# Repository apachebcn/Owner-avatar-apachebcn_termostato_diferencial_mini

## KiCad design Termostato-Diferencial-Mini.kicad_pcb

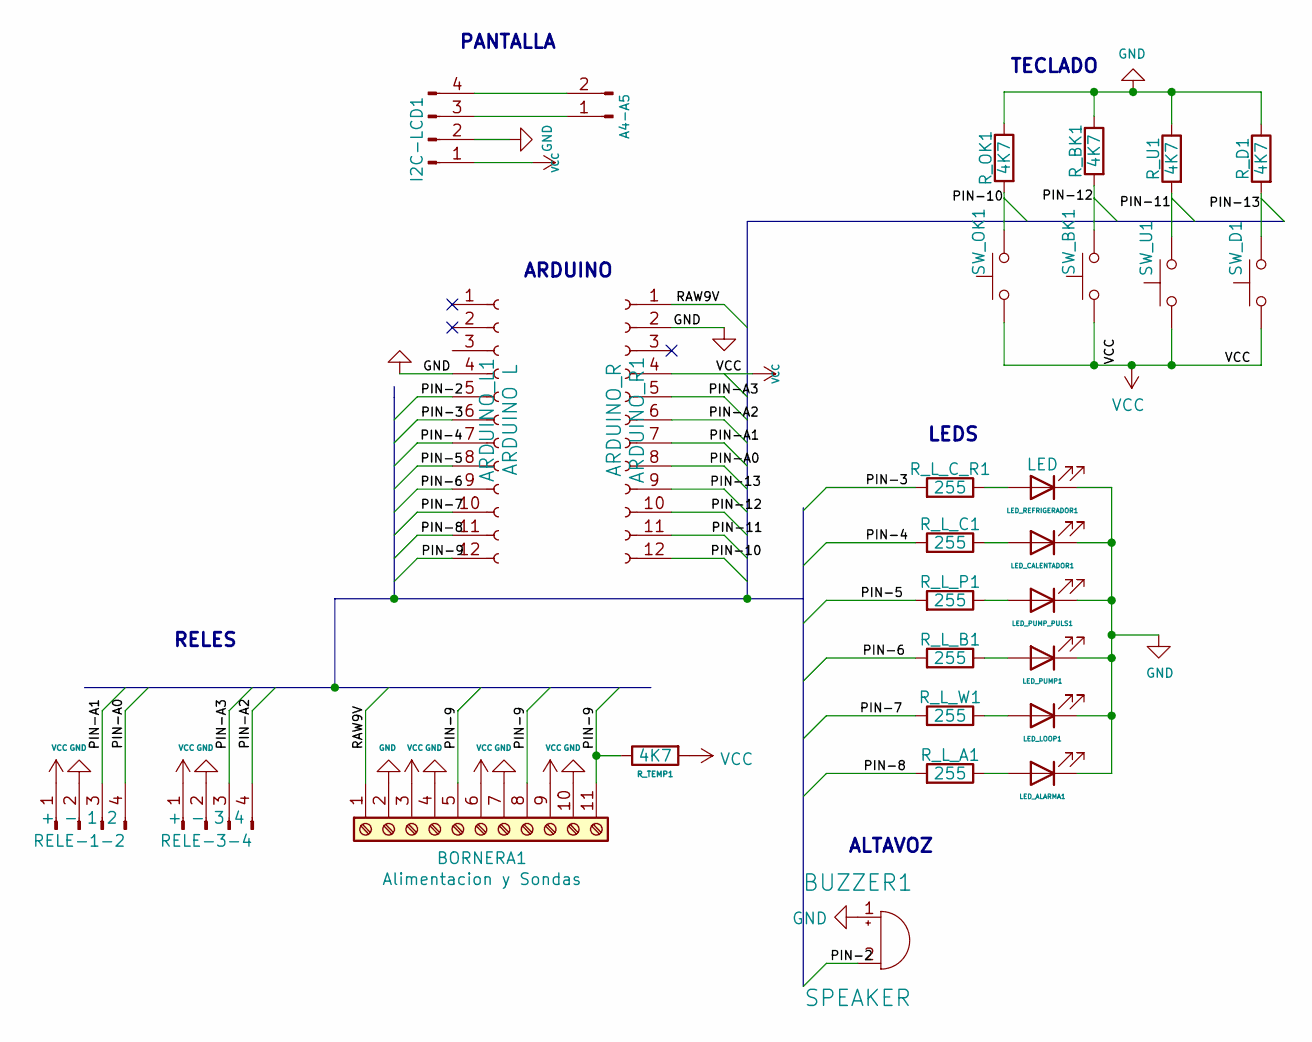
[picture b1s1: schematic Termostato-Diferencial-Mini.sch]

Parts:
A4-A5: CONN_2; PinHeader_1x02_P2.54mm_Vertical
ARDUINO_L1: ARDUINO L; PinSocket_1x13_P2.54mm_Vertical
ARDUINO_R1: ARDUINO_R; PinSocket_1x13_P2.54mm_Vertical
BORNERA1: Alimentacion y Sondas; TerminalBlock_Phoenix_MKDS-3-11-5.08_1x11_P5.08mm_Horizontal
BUZZER1: SPEAKER; Buzzer_12x9.5RM7.6
I2C-LCD1: CONN_4; PinHeader_1x04_P2.54mm_Horizontal
LED_ALARMA1: LED; LED_1206_3216Metric
LED_CALENTADOR1: LED; LED_1206_3216Metric
LED_LOOP1: LED; LED_1206_3216Metric
LED_PUMP1: LED; LED_1206_3216Metric
LED_PUMP_PULS1: LED; LED_1206_3216Metric
LED_REFRIGERADOR1: LED; LED_1206_3216Metric
RELE-1-2: + - 1 2; PinHeader_1x04_P2.54mm_Horizontal
RELE-3-4: + - 3 4; PinHeader_1x04_P2.54mm_Horizontal
R_BK1: 4K7; R_1206_3216Metric
R_D1: 4K7; R_1206_3216Metric
R_L_A1: 255; R_1206_3216Metric
R_L_B1: 255; R_1206_3216Metric
R_L_C1: 255; R_1206_3216Metric
R_L_C_R1: 255; R_1206_3216Metric
R_L_P1: 255; R_1206_3216Metric
R_L_W1: 255; R_1206_3216Metric
R_OK1: 4K7; R_1206_3216Metric
R_TEMP1: 4K7; R_1206_3216Metric
R_U1: 4K7; R_1206_3216Metric
SW_BK1: SW; SW_PUSH-12mm
SW_D1: SW; SW_PUSH-12mm
SW_OK1: SW; SW_PUSH-12mm
SW_U1: SW; SW_PUSH-12mm

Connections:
/PIN-2: ARDUINO_L1.5, BUZZER1.2 (+)
/PIN-3: ARDUINO_L1.6, R_L_C_R1.2
/PIN-4: ARDUINO_L1.7, R_L_C1.2
/PIN-5: ARDUINO_L1.8, R_L_P1.2
/PIN-6: ARDUINO_L1.9, R_L_B1.2
/PIN-7: ARDUINO_L1.10, R_L_W1.2
/PIN-8: ARDUINO_L1.11, R_L_A1.2
/PIN-9: ARDUINO_L1.12, BORNERA1.5, BORNERA1.8, BORNERA1.11, R_TEMP1.1
/PIN-10: ARDUINO_R1.12, R_OK1.2, SW_OK1.2
/PIN-11: ARDUINO_R1.11, R_U1.2, SW_U1.2
/PIN-12: ARDUINO_R1.10, R_BK1.2, SW_BK1.2
/PIN-13: ARDUINO_R1.9, R_D1.2, SW_D1.2
/PIN-A0: ARDUINO_R1.8, RELE-1-2.4
/PIN-A1: ARDUINO_R1.7, RELE-1-2.3
/PIN-A2: ARDUINO_R1.6, RELE-3-4.4
/PIN-A3: ARDUINO_R1.5, RELE-3-4.3
/RAW9V: ARDUINO_R1.1, BORNERA1.1
GND: ARDUINO_L1.4, ARDUINO_R1.2, BORNERA1.2, BORNERA1.4, BORNERA1.7, BORNERA1.10, BUZZER1.1 (-), I2C-LCD1.2, LED_ALARMA1.1 (K), LED_CALENTADOR1.1 (K), LED_LOOP1.1 (K), LED_PUMP1.1 (K), LED_PUMP_PULS1.1 (K), LED_REFRIGERADOR1.1 (K), RELE-1-2.2, RELE-3-4.2, R_BK1.1, R_D1.1, R_OK1.1, R_U1.1
unnamed: A4-A5.1, I2C-LCD1.3
unnamed: A4-A5.2, I2C-LCD1.4
unnamed: LED_ALARMA1.2 (A), R_L_A1.1
unnamed: LED_CALENTADOR1.2 (A), R_L_C1.1
unnamed: LED_LOOP1.2 (A), R_L_W1.1
unnamed: LED_PUMP1.2 (A), R_L_B1.1
unnamed: LED_PUMP_PULS1.2 (A), R_L_P1.1
unnamed: LED_REFRIGERADOR1.2 (A), R_L_C_R1.1
VCC: ARDUINO_R1.4, BORNERA1.3, BORNERA1.6, BORNERA1.9, I2C-LCD1.1, RELE-1-2.1, RELE-3-4.1, R_TEMP1.2, SW_BK1.1, SW_D1.1, SW_OK1.1, SW_U1.1

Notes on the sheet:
TECLADO
ALTAVOZ
PANTALLA
ARDUINO
RELES
LEDS

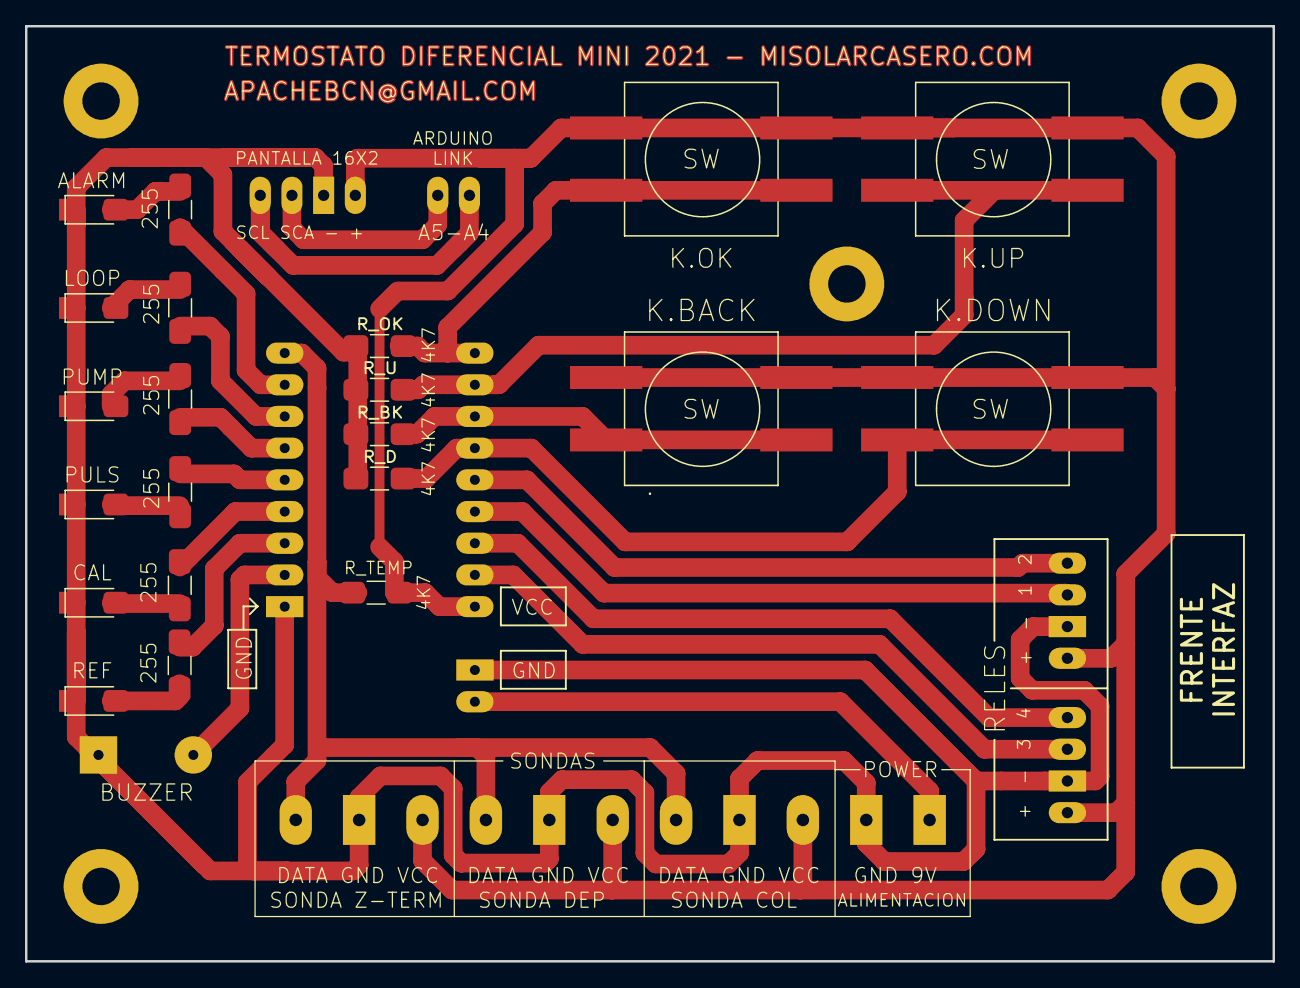
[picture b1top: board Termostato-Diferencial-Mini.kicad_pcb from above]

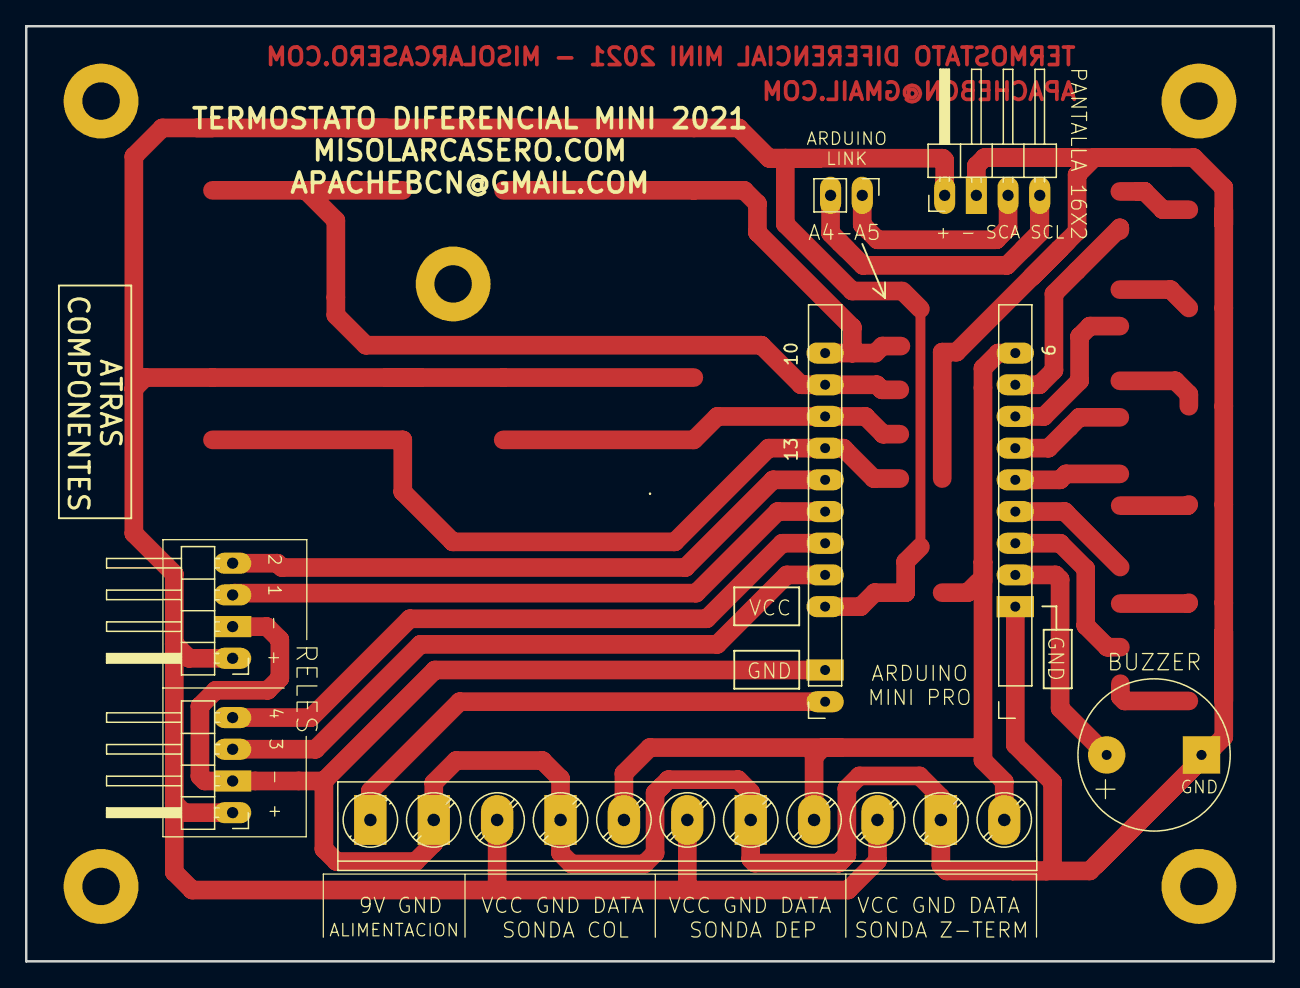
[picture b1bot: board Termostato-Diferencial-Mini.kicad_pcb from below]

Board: 2 copper layers, 100.0 x 74.9 mm, 34 parts (8 on the bottom side), 27 nets.

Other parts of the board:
TORNILLO-1, TORNILLO-1#2, TORNILLO-3, TORNILLO-4, TORNILLO-5: MountingHole_3mm_Pad
